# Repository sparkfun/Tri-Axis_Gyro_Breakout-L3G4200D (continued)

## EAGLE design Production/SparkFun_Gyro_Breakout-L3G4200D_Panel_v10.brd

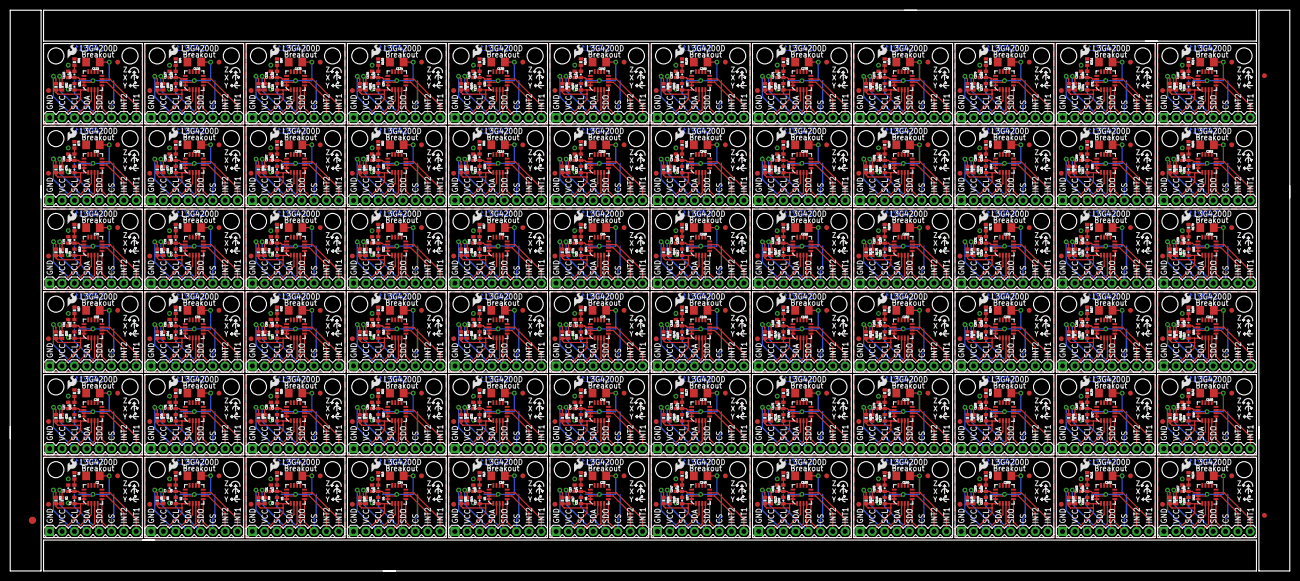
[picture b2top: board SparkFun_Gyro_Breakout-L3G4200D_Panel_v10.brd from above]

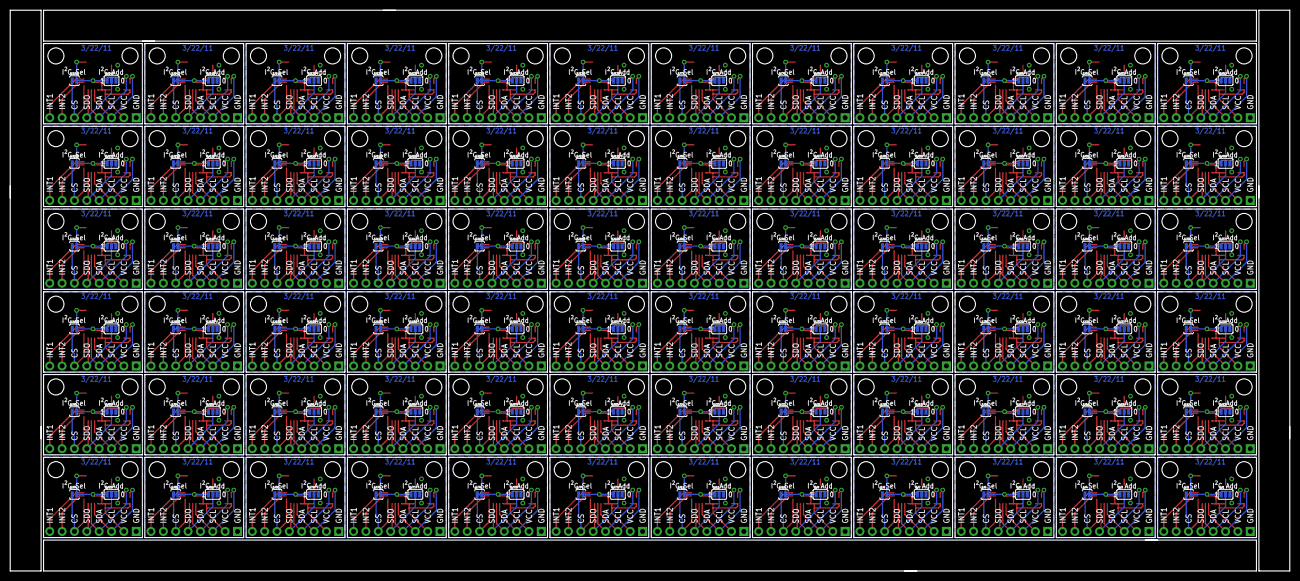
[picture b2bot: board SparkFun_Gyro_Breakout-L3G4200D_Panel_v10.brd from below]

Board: 2 copper layers, 263.1 x 115.3 mm, 1155 parts (144 on the bottom side), 720 nets.

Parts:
C1, C5, C9, C13, C17, C21, C25, C29, C33, C37, C41, C45, C49, C53, C57, C61, C65, C69, C73, C77, C81, C85, C89, C93, C97, C101, C105, C109, C113, C117, C121, C125, C129, C133, C137, C141, C145, C149, C153, C157, C161, C165, C169, C173, C177, C181, C185, C189, C193, C197, C201, C205, C209, C213, C217, C221, C225, C229, C233, C237, C241, C245, C249, C253, C257, C261, C265, C269, C273, C277, C281, C285: 0.1uF; 0402-CAP
C2, C6, C10, C14, C18, C22, C26, C30, C34, C38, C42, C46, C50, C54, C58, C62, C66, C70, C74, C78, C82, C86, C90, C94, C98, C102, C106, C110, C114, C118, C122, C126, C130, C134, C138, C142, C146, C150, C154, C158, C162, C166, C170, C174, C178, C182, C186, C190, C194, C198, C202, C206, C210, C214, C218, C222, C226, C230, C234, C238, C242, C246, C250, C254, C258, C262, C266, C270, C274, C278, C282, C286: 10uF; 1206
C3, C7, C11, C15, C19, C23, C27, C31, C35, C39, C43, C47, C51, C55, C59, C63, C67, C71, C75, C79, C83, C87, C91, C95, C99, C103, C107, C111, C115, C119, C123, C127, C131, C135, C139, C143, C147, C151, C155, C159, C163, C167, C171, C175, C179, C183, C187, C191, C195, C199, C203, C207, C211, C215, C219, C223, C227, C231, C235, C239, C243, C247, C251, C255, C259, C263, C267, C271, C275, C279, C283, C287: 10nF; 0402-CAP
C4, C8, C12, C16, C20, C24, C28, C32, C36, C40, C44, C48, C52, C56, C60, C64, C68, C72, C76, C80, C84, C88, C92, C96, C100, C104, C108, C112, C116, C120, C124, C128, C132, C136, C140, C144, C148, C152, C156, C160, C164, C168, C172, C176, C180, C184, C188, C192, C196, C200, C204, C208, C212, C216, C220, C224, C228, C232, C236, C240, C244, C248, C252, C256, C260, C264, C268, C272, C276, C280, C284, C288: 470nF; 0402-CAP
E$1: FIDUCIAL-1.5X3
E$5, E$6: FIDUCIAL-1X2
JP1, JP7, JP13, JP19, JP25, JP31, JP37, JP43, JP49, JP55, JP61, JP67, JP73, JP79, JP85, JP91, JP97, JP103, JP109, JP115, JP121, JP127, JP133, JP139, JP145, JP151, JP157, JP163, JP169, JP175, JP181, JP187, JP193, JP199, JP205, JP211, JP217, JP223, JP229, JP235, JP241, JP247, JP253, JP259, JP265, JP271, JP277, JP283, JP289, JP295, JP301, JP307, JP313, JP319, JP325, JP331, JP337, JP343, JP349, JP355, JP361, JP367, JP373, JP379, JP385, JP391, JP397, JP403, JP409, JP415, JP421, JP427: OUTPUT; 1X08
JP2, JP3, JP8, JP9, JP14, JP15, JP20, JP21, JP26, JP27, JP32, JP33, JP38, JP39, JP44, JP45, JP50, JP51, JP56, JP57, JP62, JP63, JP68, JP69, JP74, JP75, JP80, JP81, JP86, JP87, JP92, JP93, JP98, JP99, JP104, JP105, JP110, JP111, JP116, JP117, JP122, JP123, JP128, JP129, JP134, JP135, JP140, JP141, JP146, JP147, JP152, JP153, JP158, JP159, JP164, JP165, JP170, JP171, JP176, JP177, JP182, JP183, JP188, JP189, JP194, JP195, JP200, JP201, JP206, JP207, JP212, JP213, JP218, JP219, JP224, JP225, JP230, JP231, JP236, JP237, JP242, JP243, JP248, JP249, JP254, JP255, JP260, JP261, JP266, JP267, JP272, JP273, JP278, JP279, JP284, JP285, JP290, JP291, JP296, JP297, JP302, JP303, JP308, JP309, JP314, JP315, JP320, JP321, JP326, JP327, JP332, JP333, JP338, JP339, JP344, JP345, JP350, JP351, JP356, JP357, JP362, JP363, JP368, JP369, JP374, JP375, JP380, JP381, JP386, JP387, JP392, JP393, JP398, JP399, JP404, JP405, JP410, JP411, JP416, JP417, JP422, JP423, JP428, JP429: STAND-OFF
JP4, JP10, JP16, JP22, JP28, JP34, JP40, JP46, JP52, JP58, JP64, JP70, JP76, JP82, JP88, JP94, JP100, JP106, JP112, JP118, JP124, JP130, JP136, JP142, JP148, JP154, JP160, JP166, JP172, JP178, JP184, JP190, JP196, JP202, JP208, JP214, JP220, JP226, JP232, JP238, JP244, JP250, JP256, JP262, JP268, JP274, JP280, JP286, JP292, JP298, JP304, JP310, JP316, JP322, JP328, JP334, JP340, JP346, JP352, JP358, JP364, JP370, JP376, JP382, JP388, JP394, JP400, JP406, JP412, JP418, JP424, JP430: LOGO-SFESK; SFE-LOGO-FLAME
JP5, JP6, JP11, JP12, JP17, JP18, JP23, JP24, JP29, JP30, JP35, JP36, JP41, JP42, JP47, JP48, JP53, JP54, JP59, JP60, JP65, JP66, JP71, JP72, JP77, JP78, JP83, JP84, JP89, JP90, JP95, JP96, JP101, JP102, JP107, JP108, JP113, JP114, JP119, JP120, JP125, JP126, JP131, JP132, JP137, JP138, JP143, JP144, JP149, JP150, JP155, JP156, JP161, JP162, JP167, JP168, JP173, JP174, JP179, JP180, JP185, JP186, JP191, JP192, JP197, JP198, JP203, JP204, JP209, JP210, JP215, JP216, JP221, JP222, JP227, JP228, JP233, JP234, JP239, JP240, JP245, JP246, JP251, JP252, JP257, JP258, JP263, JP264, JP269, JP270, JP275, JP276, JP281, JP282, JP287, JP288, JP293, JP294, JP299, JP300, JP305, JP306, JP311, JP312, JP317, JP318, JP323, JP324, JP329, JP330, JP335, JP336, JP341, JP342, JP347, JP348, JP353, JP354, JP359, JP360, JP365, JP366, JP371, JP372, JP377, JP378, JP383, JP384, JP389, JP390, JP395, JP396, JP401, JP402, JP407, JP408, JP413, JP414, JP419, JP420, JP425, JP426, JP431, JP432: FIDUCIAL1X2; FIDUCIAL-1X2
R1, R2, R3, R4, R5, R6, R7, R8, R9, R10, R11, R12, R13, R14, R15, R16, R17, R18, R19, R20, R21, R22, R23, R24, R25, R26, R27, R28, R29, R30, R31, R32, R33, R34, R35, R36, R37, R38, R39, R40, R41, R42, R43, R44, R45, R46, R47, R48, R49, R50, R51, R52, R53, R54, R55, R56, R57, R58, R59, R60, R61, R62, R63, R64, R65, R66, R67, R68, R69, R70, R71, R72, R73, R74, R75, R76, R77, R78, R79, R80, R81, R82, R83, R84, R85, R86, R87, R88, R89, R90, R91, R92, R93, R94, R95, R96, R97, R98, R99, R100, R101, R102, R103, R104, R105, R106, R107, R108, R109, R110, R111, R112, R113, R114, R115, R116, R117, R118, R119, R120, R121, R122, R123, R124, R125, R126, R127, R128, R129, R130, R131, R132, R133, R134, R135, R136, R137, R138, R139, R140, R141, R142, R143, R144, R145, R146, R147, R148, R149, R150, R151, R152, R153, R154, R155, R156, R157, R158, R159, R160, R161, R162, R163, R164, R165, R166, R167, R168, R169, R170, R171, R172, R173, R174, R175, R176, R177, R178, R179, R180, R181, R182, R183, R184, R185, R186, R187, R188, R189, R190, R191, R192, R193, R194, R195, R196, R197, R198, R199, R200, R201, R202, R203, R204, R205, R206, R207, R208, R209, R210, R211, R212, R213, R214, R215, R216: 10k; 0402-RES
SJ1, SJ3, SJ5, SJ7, SJ9, SJ11, SJ13, SJ15, SJ17, SJ19, SJ21, SJ23, SJ25, SJ27, SJ29, SJ31, SJ33, SJ35, SJ37, SJ39, SJ41, SJ43, SJ45, SJ47, SJ49, SJ51, SJ53, SJ55, SJ57, SJ59, SJ61, SJ63, SJ65, SJ67, SJ69, SJ71, SJ73, SJ75, SJ77, SJ79, SJ81, SJ83, SJ85, SJ87, SJ89, SJ91, SJ93, SJ95, SJ97, SJ99, SJ101, SJ103, SJ105, SJ107, SJ109, SJ111, SJ113, SJ115, SJ117, SJ119, SJ121, SJ123, SJ125, SJ127, SJ129, SJ131, SJ133, SJ135, SJ137, SJ139, SJ141, SJ143: I2C-Add; SJ_3
SJ2, SJ4, SJ6, SJ8, SJ10, SJ12, SJ14, SJ16, SJ18, SJ20, SJ22, SJ24, SJ26, SJ28, SJ30, SJ32, SJ34, SJ36, SJ38, SJ40, SJ42, SJ44, SJ46, SJ48, SJ50, SJ52, SJ54, SJ56, SJ58, SJ60, SJ62, SJ64, SJ66, SJ68, SJ70, SJ72, SJ74, SJ76, SJ78, SJ80, SJ82, SJ84, SJ86, SJ88, SJ90, SJ92, SJ94, SJ96, SJ98, SJ100, SJ102, SJ104, SJ106, SJ108, SJ110, SJ112, SJ114, SJ116, SJ118, SJ120, SJ122, SJ124, SJ126, SJ128, SJ130, SJ132, SJ134, SJ136, SJ138, SJ140, SJ142, SJ144: I2C-Mode; SJ_2S-NO
U1, U2, U3, U4, U5, U6, U7, U8, U9, U10, U11, U12, U13, U14, U15, U16, U17, U18, U19, U20, U21, U22, U23, U24, U25, U26, U27, U28, U29, U30, U31, U32, U33, U34, U35, U36, U37, U38, U39, U40, U41, U42, U43, U44, U45, U46, U47, U48, U49, U50, U51, U52, U53, U54, U55, U56, U57, U58, U59, U60, U61, U62, U63, U64, U65, U66, U67, U68, U69, U70, U71, U72: L3G4200D; LGA16-4X4

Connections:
CS: JP1.6, SJ2.1, U1.5
CS1: JP7.6, SJ4.1, U2.5
CS2: JP13.6, SJ6.1, U3.5
CS3: JP19.6, SJ8.1, U4.5
CS4: JP25.6, SJ10.1, U5.5
CS5: JP31.6, SJ12.1, U6.5
CS6: JP37.6, SJ14.1, U7.5
CS7: JP43.6, SJ16.1, U8.5
CS8: JP49.6, SJ18.1, U9.5
CS9: JP55.6, SJ20.1, U10.5
CS10: JP61.6, SJ22.1, U11.5
CS11: JP67.6, SJ24.1, U12.5
CS12: JP73.6, SJ26.1, U13.5
CS13: JP79.6, SJ28.1, U14.5
CS14: JP85.6, SJ30.1, U15.5
CS15: JP91.6, SJ32.1, U16.5
CS16: JP97.6, SJ34.1, U17.5
CS17: JP103.6, SJ36.1, U18.5
CS18: JP109.6, SJ38.1, U19.5
CS19: JP115.6, SJ40.1, U20.5
CS20: JP121.6, SJ42.1, U21.5
CS21: JP127.6, SJ44.1, U22.5
CS22: JP133.6, SJ46.1, U23.5
CS23: JP139.6, SJ48.1, U24.5
CS24: JP145.6, SJ50.1, U25.5
CS25: JP151.6, SJ52.1, U26.5
CS26: JP157.6, SJ54.1, U27.5
CS27: JP163.6, SJ56.1, U28.5
CS28: JP169.6, SJ58.1, U29.5
CS29: JP175.6, SJ60.1, U30.5
CS30: JP181.6, SJ62.1, U31.5
CS31: JP187.6, SJ64.1, U32.5
CS32: JP193.6, SJ66.1, U33.5
CS33: JP199.6, SJ68.1, U34.5
CS34: JP205.6, SJ70.1, U35.5
CS35: JP211.6, SJ72.1, U36.5
CS36: JP217.6, SJ74.1, U37.5
CS37: JP223.6, SJ76.1, U38.5
CS38: JP229.6, SJ78.1, U39.5
CS39: JP235.6, SJ80.1, U40.5
CS40: JP241.6, SJ82.1, U41.5
CS41: JP247.6, SJ84.1, U42.5
CS42: JP253.6, SJ86.1, U43.5
CS43: JP259.6, SJ88.1, U44.5
CS44: JP265.6, SJ90.1, U45.5
CS45: JP271.6, SJ92.1, U46.5
CS46: JP277.6, SJ94.1, U47.5
CS47: JP283.6, SJ96.1, U48.5
CS48: JP289.6, SJ98.1, U49.5
CS49: JP295.6, SJ100.1, U50.5
CS50: JP301.6, SJ102.1, U51.5
CS51: JP307.6, SJ104.1, U52.5
CS52: JP313.6, SJ106.1, U53.5
CS53: JP319.6, SJ108.1, U54.5
CS54: JP325.6, SJ110.1, U55.5
CS55: JP331.6, SJ112.1, U56.5
CS56: JP337.6, SJ114.1, U57.5
CS57: JP343.6, SJ116.1, U58.5
CS58: JP349.6, SJ118.1, U59.5
CS59: JP355.6, SJ120.1, U60.5
CS60: JP361.6, SJ122.1, U61.5
CS61: JP367.6, SJ124.1, U62.5
CS62: JP373.6, SJ126.1, U63.5
CS63: JP379.6, SJ128.1, U64.5
CS64: JP385.6, SJ130.1, U65.5
CS65: JP391.6, SJ132.1, U66.5
CS66: JP397.6, SJ134.1, U67.5
CS67: JP403.6, SJ136.1, U68.5
CS68: JP409.6, SJ138.1, U69.5
CS69: JP415.6, SJ140.1, U70.5
CS70: JP421.6, SJ142.1, U71.5
CS71: JP427.6, SJ144.1, U72.5
GND: C1.2, C2.2, C3.2, JP1.1, R1.1, SJ1.3, U1.8, U1.9, U1.10, U1.11, U1.12, U1.13
GND1: C5.2, C6.2, C7.2, JP7.1, R4.1, SJ3.3, U2.8, U2.9, U2.10, U2.11, U2.12, U2.13
GND2: C9.2, C10.2, C11.2, JP13.1, R7.1, SJ5.3, U3.8, U3.9, U3.10, U3.11, U3.12, U3.13
GND3: C13.2, C14.2, C15.2, JP19.1, R10.1, SJ7.3, U4.8, U4.9, U4.10, U4.11, U4.12, U4.13
GND4: C17.2, C18.2, C19.2, JP25.1, R13.1, SJ9.3, U5.8, U5.9, U5.10, U5.11, U5.12, U5.13
GND5: C21.2, C22.2, C23.2, JP31.1, R16.1, SJ11.3, U6.8, U6.9, U6.10, U6.11, U6.12, U6.13
GND6: C25.2, C26.2, C27.2, JP37.1, R19.1, SJ13.3, U7.8, U7.9, U7.10, U7.11, U7.12, U7.13
GND7: C29.2, C30.2, C31.2, JP43.1, R22.1, SJ15.3, U8.8, U8.9, U8.10, U8.11, U8.12, U8.13
GND8: C33.2, C34.2, C35.2, JP49.1, R25.1, SJ17.3, U9.8, U9.9, U9.10, U9.11, U9.12, U9.13
GND9: C37.2, C38.2, C39.2, JP55.1, R28.1, SJ19.3, U10.8, U10.9, U10.10, U10.11, U10.12, U10.13
GND10: C41.2, C42.2, C43.2, JP61.1, R31.1, SJ21.3, U11.8, U11.9, U11.10, U11.11, U11.12, U11.13
GND11: C45.2, C46.2, C47.2, JP67.1, R34.1, SJ23.3, U12.8, U12.9, U12.10, U12.11, U12.12, U12.13
GND12: C49.2, C50.2, C51.2, JP73.1, R37.1, SJ25.3, U13.8, U13.9, U13.10, U13.11, U13.12, U13.13
GND13: C53.2, C54.2, C55.2, JP79.1, R40.1, SJ27.3, U14.8, U14.9, U14.10, U14.11, U14.12, U14.13
GND14: C57.2, C58.2, C59.2, JP85.1, R43.1, SJ29.3, U15.8, U15.9, U15.10, U15.11, U15.12, U15.13
GND15: C61.2, C62.2, C63.2, JP91.1, R46.1, SJ31.3, U16.8, U16.9, U16.10, U16.11, U16.12, U16.13
GND16: C65.2, C66.2, C67.2, JP97.1, R49.1, SJ33.3, U17.8, U17.9, U17.10, U17.11, U17.12, U17.13
GND17: C69.2, C70.2, C71.2, JP103.1, R52.1, SJ35.3, U18.8, U18.9, U18.10, U18.11, U18.12, U18.13
GND18: C73.2, C74.2, C75.2, JP109.1, R55.1, SJ37.3, U19.8, U19.9, U19.10, U19.11, U19.12, U19.13
GND19: C77.2, C78.2, C79.2, JP115.1, R58.1, SJ39.3, U20.8, U20.9, U20.10, U20.11, U20.12, U20.13
GND20: C81.2, C82.2, C83.2, JP121.1, R61.1, SJ41.3, U21.8, U21.9, U21.10, U21.11, U21.12, U21.13
GND21: C85.2, C86.2, C87.2, JP127.1, R64.1, SJ43.3, U22.8, U22.9, U22.10, U22.11, U22.12, U22.13
GND22: C89.2, C90.2, C91.2, JP133.1, R67.1, SJ45.3, U23.8, U23.9, U23.10, U23.11, U23.12, U23.13
GND23: C93.2, C94.2, C95.2, JP139.1, R70.1, SJ47.3, U24.8, U24.9, U24.10, U24.11, U24.12, U24.13
GND24: C97.2, C98.2, C99.2, JP145.1, R73.1, SJ49.3, U25.8, U25.9, U25.10, U25.11, U25.12, U25.13
GND25: C101.2, C102.2, C103.2, JP151.1, R76.1, SJ51.3, U26.8, U26.9, U26.10, U26.11, U26.12, U26.13
GND26: C105.2, C106.2, C107.2, JP157.1, R79.1, SJ53.3, U27.8, U27.9, U27.10, U27.11, U27.12, U27.13
GND27: C109.2, C110.2, C111.2, JP163.1, R82.1, SJ55.3, U28.8, U28.9, U28.10, U28.11, U28.12, U28.13
GND28: C113.2, C114.2, C115.2, JP169.1, R85.1, SJ57.3, U29.8, U29.9, U29.10, U29.11, U29.12, U29.13
GND29: C117.2, C118.2, C119.2, JP175.1, R88.1, SJ59.3, U30.8, U30.9, U30.10, U30.11, U30.12, U30.13
GND30: C121.2, C122.2, C123.2, JP181.1, R91.1, SJ61.3, U31.8, U31.9, U31.10, U31.11, U31.12, U31.13
GND31: C125.2, C126.2, C127.2, JP187.1, R94.1, SJ63.3, U32.8, U32.9, U32.10, U32.11, U32.12, U32.13
GND32: C129.2, C130.2, C131.2, JP193.1, R97.1, SJ65.3, U33.8, U33.9, U33.10, U33.11, U33.12, U33.13
GND33: C133.2, C134.2, C135.2, JP199.1, R100.1, SJ67.3, U34.8, U34.9, U34.10, U34.11, U34.12, U34.13
GND34: C137.2, C138.2, C139.2, JP205.1, R103.1, SJ69.3, U35.8, U35.9, U35.10, U35.11, U35.12, U35.13
GND35: C141.2, C142.2, C143.2, JP211.1, R106.1, SJ71.3, U36.8, U36.9, U36.10, U36.11, U36.12, U36.13
GND36: C145.2, C146.2, C147.2, JP217.1, R109.1, SJ73.3, U37.8, U37.9, U37.10, U37.11, U37.12, U37.13
GND37: C149.2, C150.2, C151.2, JP223.1, R112.1, SJ75.3, U38.8, U38.9, U38.10, U38.11, U38.12, U38.13
GND38: C153.2, C154.2, C155.2, JP229.1, R115.1, SJ77.3, U39.8, U39.9, U39.10, U39.11, U39.12, U39.13
GND39: C157.2, C158.2, C159.2, JP235.1, R118.1, SJ79.3, U40.8, U40.9, U40.10, U40.11, U40.12, U40.13
GND40: C161.2, C162.2, C163.2, JP241.1, R121.1, SJ81.3, U41.8, U41.9, U41.10, U41.11, U41.12, U41.13
GND41: C165.2, C166.2, C167.2, JP247.1, R124.1, SJ83.3, U42.8, U42.9, U42.10, U42.11, U42.12, U42.13
GND42: C169.2, C170.2, C171.2, JP253.1, R127.1, SJ85.3, U43.8, U43.9, U43.10, U43.11, U43.12, U43.13
GND43: C173.2, C174.2, C175.2, JP259.1, R130.1, SJ87.3, U44.8, U44.9, U44.10, U44.11, U44.12, U44.13
GND44: C177.2, C178.2, C179.2, JP265.1, R133.1, SJ89.3, U45.8, U45.9, U45.10, U45.11, U45.12, U45.13
GND45: C181.2, C182.2, C183.2, JP271.1, R136.1, SJ91.3, U46.8, U46.9, U46.10, U46.11, U46.12, U46.13
GND46: C185.2, C186.2, C187.2, JP277.1, R139.1, SJ93.3, U47.8, U47.9, U47.10, U47.11, U47.12, U47.13
GND47: C189.2, C190.2, C191.2, JP283.1, R142.1, SJ95.3, U48.8, U48.9, U48.10, U48.11, U48.12, U48.13
GND48: C193.2, C194.2, C195.2, JP289.1, R145.1, SJ97.3, U49.8, U49.9, U49.10, U49.11, U49.12, U49.13
GND49: C197.2, C198.2, C199.2, JP295.1, R148.1, SJ99.3, U50.8, U50.9, U50.10, U50.11, U50.12, U50.13
GND50: C201.2, C202.2, C203.2, JP301.1, R151.1, SJ101.3, U51.8, U51.9, U51.10, U51.11, U51.12, U51.13
GND51: C205.2, C206.2, C207.2, JP307.1, R154.1, SJ103.3, U52.8, U52.9, U52.10, U52.11, U52.12, U52.13
GND52: C209.2, C210.2, C211.2, JP313.1, R157.1, SJ105.3, U53.8, U53.9, U53.10, U53.11, U53.12, U53.13
GND53: C213.2, C214.2, C215.2, JP319.1, R160.1, SJ107.3, U54.8, U54.9, U54.10, U54.11, U54.12, U54.13
GND54: C217.2, C218.2, C219.2, JP325.1, R163.1, SJ109.3, U55.8, U55.9, U55.10, U55.11, U55.12, U55.13
GND55: C221.2, C222.2, C223.2, JP331.1, R166.1, SJ111.3, U56.8, U56.9, U56.10, U56.11, U56.12, U56.13
GND56: C225.2, C226.2, C227.2, JP337.1, R169.1, SJ113.3, U57.8, U57.9, U57.10, U57.11, U57.12, U57.13
GND57: C229.2, C230.2, C231.2, JP343.1, R172.1, SJ115.3, U58.8, U58.9, U58.10, U58.11, U58.12, U58.13
GND58: C233.2, C234.2, C235.2, JP349.1, R175.1, SJ117.3, U59.8, U59.9, U59.10, U59.11, U59.12, U59.13
GND59: C237.2, C238.2, C239.2, JP355.1, R178.1, SJ119.3, U60.8, U60.9, U60.10, U60.11, U60.12, U60.13
GND60: C241.2, C242.2, C243.2, JP361.1, R181.1, SJ121.3, U61.8, U61.9, U61.10, U61.11, U61.12, U61.13
GND61: C245.2, C246.2, C247.2, JP367.1, R184.1, SJ123.3, U62.8, U62.9, U62.10, U62.11, U62.12, U62.13
GND62: C249.2, C250.2, C251.2, JP373.1, R187.1, SJ125.3, U63.8, U63.9, U63.10, U63.11, U63.12, U63.13
GND63: C253.2, C254.2, C255.2, JP379.1, R190.1, SJ127.3, U64.8, U64.9, U64.10, U64.11, U64.12, U64.13
GND64: C257.2, C258.2, C259.2, JP385.1, R193.1, SJ129.3, U65.8, U65.9, U65.10, U65.11, U65.12, U65.13
GND65: C261.2, C262.2, C263.2, JP391.1, R196.1, SJ131.3, U66.8, U66.9, U66.10, U66.11, U66.12, U66.13
GND66: C265.2, C266.2, C267.2, JP397.1, R199.1, SJ133.3, U67.8, U67.9, U67.10, U67.11, U67.12, U67.13
GND67: C269.2, C270.2, C271.2, JP403.1, R202.1, SJ135.3, U68.8, U68.9, U68.10, U68.11, U68.12, U68.13
GND68: C273.2, C274.2, C275.2, JP409.1, R205.1, SJ137.3, U69.8, U69.9, U69.10, U69.11, U69.12, U69.13
GND69: C277.2, C278.2, C279.2, JP415.1, R208.1, SJ139.3, U70.8, U70.9, U70.10, U70.11, U70.12, U70.13
GND70: C281.2, C282.2, C283.2, JP421.1, R211.1, SJ141.3, U71.8, U71.9, U71.10, U71.11, U71.12, U71.13
GND71: C285.2, C286.2, C287.2, JP427.1, R214.1, SJ143.3, U72.8, U72.9, U72.10, U72.11, U72.12, U72.13
INT1: JP1.8, U1.7
INT2: JP1.7, U1.6
INT3: JP7.8, U2.7
INT4: JP7.7, U2.6
INT5: JP13.8, U3.7
INT6: JP13.7, U3.6
INT7: JP19.8, U4.7
INT8: JP19.7, U4.6
INT9: JP25.8, U5.7
INT10: JP25.7, U5.6
INT11: JP31.8, U6.7
INT12: JP31.7, U6.6
INT13: JP37.8, U7.7
INT14: JP37.7, U7.6
INT15: JP43.8, U8.7
INT16: JP43.7, U8.6
INT17: JP49.8, U9.7
INT18: JP49.7, U9.6
INT19: JP55.8, U10.7
INT20: JP55.7, U10.6
INT21: JP61.8, U11.7
INT22: JP61.7, U11.6
INT23: JP67.8, U12.7
INT24: JP67.7, U12.6
INT25: JP73.8, U13.7
INT26: JP73.7, U13.6
INT27: JP79.8, U14.7
INT28: JP79.7, U14.6
INT29: JP85.8, U15.7
INT30: JP85.7, U15.6
INT31: JP91.8, U16.7
INT32: JP91.7, U16.6
INT33: JP97.8, U17.7
INT34: JP97.7, U17.6
INT35: JP103.8, U18.7
INT36: JP103.7, U18.6
INT37: JP109.8, U19.7
INT38: JP109.7, U19.6
INT39: JP115.8, U20.7
INT40: JP115.7, U20.6
INT41: JP121.8, U21.7
INT42: JP121.7, U21.6
INT43: JP127.8, U22.7
INT44: JP127.7, U22.6
INT45: JP133.8, U23.7
INT46: JP133.7, U23.6
INT47: JP139.8, U24.7
INT48: JP139.7, U24.6
INT49: JP145.8, U25.7
INT50: JP145.7, U25.6
INT51: JP151.8, U26.7
INT52: JP151.7, U26.6
INT53: JP157.8, U27.7
INT54: JP157.7, U27.6
INT55: JP163.8, U28.7
INT56: JP163.7, U28.6
INT57: JP169.8, U29.7
INT58: JP169.7, U29.6
INT59: JP175.8, U30.7
INT60: JP175.7, U30.6
INT61: JP181.8, U31.7
INT62: JP181.7, U31.6
INT63: JP187.8, U32.7
INT64: JP187.7, U32.6
INT65: JP193.8, U33.7
INT66: JP193.7, U33.6
INT67: JP199.8, U34.7
INT68: JP199.7, U34.6
INT69: JP205.8, U35.7
INT70: JP205.7, U35.6
INT71: JP211.8, U36.7
INT72: JP211.7, U36.6
INT73: JP217.8, U37.7
INT74: JP217.7, U37.6
INT75: JP223.8, U38.7
INT76: JP223.7, U38.6
INT77: JP229.8, U39.7
INT78: JP229.7, U39.6
INT79: JP235.8, U40.7
INT80: JP235.7, U40.6
INT81: JP241.8, U41.7
INT82: JP241.7, U41.6
INT83: JP247.8, U42.7
INT84: JP247.7, U42.6
INT85: JP253.8, U43.7
INT86: JP253.7, U43.6
INT87: JP259.8, U44.7
INT88: JP259.7, U44.6
INT89: JP265.8, U45.7
INT90: JP265.7, U45.6
INT91: JP271.8, U46.7
INT92: JP271.7, U46.6
INT93: JP277.8, U47.7
INT94: JP277.7, U47.6
INT95: JP283.8, U48.7
INT96: JP283.7, U48.6
INT97: JP289.8, U49.7
INT98: JP289.7, U49.6
INT99: JP295.8, U50.7
INT100: JP295.7, U50.6
INT101: JP301.8, U51.7
INT102: JP301.7, U51.6
INT103: JP307.8, U52.7
INT104: JP307.7, U52.6
INT105: JP313.8, U53.7
INT106: JP313.7, U53.6
INT107: JP319.8, U54.7
INT108: JP319.7, U54.6
INT109: JP325.8, U55.7
INT110: JP325.7, U55.6
INT111: JP331.8, U56.7
INT112: JP331.7, U56.6
INT113: JP337.8, U57.7
INT114: JP337.7, U57.6
INT115: JP343.8, U58.7
INT116: JP343.7, U58.6
INT117: JP349.8, U59.7
INT118: JP349.7, U59.6
INT119: JP355.8, U60.7
INT120: JP355.7, U60.6
INT121: JP361.8, U61.7
INT122: JP361.7, U61.6
INT123: JP367.8, U62.7
INT124: JP367.7, U62.6
INT125: JP373.8, U63.7
INT126: JP373.7, U63.6
INT127: JP379.8, U64.7
INT128: JP379.7, U64.6
INT129: JP385.8, U65.7
INT130: JP385.7, U65.6
INT131: JP391.8, U66.7
INT132: JP391.7, U66.6
INT133: JP397.8, U67.7
INT134: JP397.7, U67.6
INT135: JP403.8, U68.7
INT136: JP403.7, U68.6
INT137: JP409.8, U69.7
INT138: JP409.7, U69.6
INT139: JP415.8, U70.7
INT140: JP415.7, U70.6
INT141: JP421.8, U71.7
INT142: JP421.7, U71.6
INT143: JP427.8, U72.7
INT144: JP427.7, U72.6
PLL: C3.1, C4.1, U1.14
PLL1: C7.1, C8.1, U2.14
PLL2: C11.1, C12.1, U3.14
PLL3: C15.1, C16.1, U4.14
PLL4: C19.1, C20.1, U5.14
PLL5: C23.1, C24.1, U6.14
PLL6: C27.1, C28.1, U7.14
PLL7: C31.1, C32.1, U8.14
PLL8: C35.1, C36.1, U9.14
PLL9: C39.1, C40.1, U10.14
PLL10: C43.1, C44.1, U11.14
PLL11: C47.1, C48.1, U12.14
PLL12: C51.1, C52.1, U13.14
PLL13: C55.1, C56.1, U14.14
PLL14: C59.1, C60.1, U15.14
PLL15: C63.1, C64.1, U16.14
PLL16: C67.1, C68.1, U17.14
PLL17: C71.1, C72.1, U18.14
PLL18: C75.1, C76.1, U19.14
PLL19: C79.1, C80.1, U20.14
PLL20: C83.1, C84.1, U21.14
PLL21: C87.1, C88.1, U22.14
PLL22: C91.1, C92.1, U23.14
PLL23: C95.1, C96.1, U24.14
PLL24: C99.1, C100.1, U25.14
PLL25: C103.1, C104.1, U26.14
PLL26: C107.1, C108.1, U27.14
PLL27: C111.1, C112.1, U28.14
PLL28: C115.1, C116.1, U29.14
PLL29: C119.1, C120.1, U30.14
PLL30: C123.1, C124.1, U31.14
PLL31: C127.1, C128.1, U32.14
PLL32: C131.1, C132.1, U33.14
PLL33: C135.1, C136.1, U34.14
PLL34: C139.1, C140.1, U35.14
PLL35: C143.1, C144.1, U36.14
PLL36: C147.1, C148.1, U37.14
PLL37: C151.1, C152.1, U38.14
PLL38: C155.1, C156.1, U39.14
PLL39: C159.1, C160.1, U40.14
PLL40: C163.1, C164.1, U41.14
PLL41: C167.1, C168.1, U42.14
PLL42: C171.1, C172.1, U43.14
PLL43: C175.1, C176.1, U44.14
PLL44: C179.1, C180.1, U45.14
PLL45: C183.1, C184.1, U46.14
PLL46: C187.1, C188.1, U47.14
PLL47: C191.1, C192.1, U48.14
PLL48: C195.1, C196.1, U49.14
PLL49: C199.1, C200.1, U50.14
PLL50: C203.1, C204.1, U51.14
PLL51: C207.1, C208.1, U52.14
PLL52: C211.1, C212.1, U53.14
PLL53: C215.1, C216.1, U54.14
PLL54: C219.1, C220.1, U55.14
PLL55: C223.1, C224.1, U56.14
PLL56: C227.1, C228.1, U57.14
PLL57: C231.1, C232.1, U58.14
PLL58: C235.1, C236.1, U59.14
PLL59: C239.1, C240.1, U60.14
PLL60: C243.1, C244.1, U61.14
PLL61: C247.1, C248.1, U62.14
PLL62: C251.1, C252.1, U63.14
PLL63: C255.1, C256.1, U64.14
PLL64: C259.1, C260.1, U65.14
PLL65: C263.1, C264.1, U66.14
PLL66: C267.1, C268.1, U67.14
PLL67: C271.1, C272.1, U68.14
PLL68: C275.1, C276.1, U69.14
PLL69: C279.1, C280.1, U70.14
PLL70: C283.1, C284.1, U71.14
PLL71: C287.1, C288.1, U72.14
PLL-1: C8.2, R4.2
PLL-2: C4.2, R1.2
PLL-3: C12.2, R7.2
PLL-4: C16.2, R10.2
PLL-5: C20.2, R13.2
PLL-6: C24.2, R16.2
PLL-7: C28.2, R19.2
PLL-8: C32.2, R22.2
PLL-9: C36.2, R25.2
PLL-10: C40.2, R28.2
PLL-11: C44.2, R31.2
PLL-12: C48.2, R34.2
PLL-13: C52.2, R37.2
PLL-14: C56.2, R40.2
PLL-15: C60.2, R43.2
PLL-16: C64.2, R46.2
PLL-17: C68.2, R49.2
PLL-18: C72.2, R52.2
PLL-19: C76.2, R55.2
PLL-20: C80.2, R58.2
PLL-21: C84.2, R61.2
PLL-22: C88.2, R64.2
PLL-23: C92.2, R67.2
PLL-24: C96.2, R70.2
PLL-25: C100.2, R73.2
PLL-26: C104.2, R76.2
PLL-27: C108.2, R79.2
PLL-28: C112.2, R82.2
PLL-29: C116.2, R85.2
PLL-30: C120.2, R88.2
PLL-31: C124.2, R91.2
PLL-32: C128.2, R94.2
PLL-33: C132.2, R97.2
PLL-34: C136.2, R100.2
PLL-35: C140.2, R103.2
PLL-36: C144.2, R106.2
PLL-37: C148.2, R109.2
PLL-38: C152.2, R112.2
PLL-39: C156.2, R115.2
PLL-40: C160.2, R118.2
PLL-41: C164.2, R121.2
PLL-42: C168.2, R124.2
PLL-43: C172.2, R127.2
PLL-44: C176.2, R130.2
PLL-45: C180.2, R133.2
PLL-46: C184.2, R136.2
PLL-47: C188.2, R139.2
PLL-48: C192.2, R142.2
PLL-49: C196.2, R145.2
PLL-50: C200.2, R148.2
PLL-51: C204.2, R151.2
PLL-52: C208.2, R154.2
PLL-53: C212.2, R157.2
PLL-54: C216.2, R160.2
PLL-55: C220.2, R163.2
PLL-56: C224.2, R166.2
PLL-57: C228.2, R169.2
PLL-58: C232.2, R172.2
PLL-59: C236.2, R175.2
PLL-60: C240.2, R178.2
PLL-61: C244.2, R181.2
PLL-62: C248.2, R184.2
PLL-63: C252.2, R187.2
PLL-64: C256.2, R190.2
PLL-65: C260.2, R193.2
PLL-66: C264.2, R196.2
PLL-67: C268.2, R199.2
PLL-68: C272.2, R202.2
PLL-69: C276.2, R205.2
PLL-70: C280.2, R208.2
PLL-71: C284.2, R211.2
PLL-72: C288.2, R214.2
SCL: JP1.3, R3.1, U1.2
SCL1: JP7.3, R6.1, U2.2
SCL2: JP13.3, R9.1, U3.2
SCL3: JP19.3, R12.1, U4.2
SCL4: JP25.3, R15.1, U5.2
SCL5: JP31.3, R18.1, U6.2
SCL6: JP37.3, R21.1, U7.2
SCL7: JP43.3, R24.1, U8.2
SCL8: JP49.3, R27.1, U9.2
SCL9: JP55.3, R30.1, U10.2
SCL10: JP61.3, R33.1, U11.2
SCL11: JP67.3, R36.1, U12.2
SCL12: JP73.3, R39.1, U13.2
SCL13: JP79.3, R42.1, U14.2
SCL14: JP85.3, R45.1, U15.2
SCL15: JP91.3, R48.1, U16.2
SCL16: JP97.3, R51.1, U17.2
SCL17: JP103.3, R54.1, U18.2
SCL18: JP109.3, R57.1, U19.2
SCL19: JP115.3, R60.1, U20.2
SCL20: JP121.3, R63.1, U21.2
SCL21: JP127.3, R66.1, U22.2
SCL22: JP133.3, R69.1, U23.2
SCL23: JP139.3, R72.1, U24.2
SCL24: JP145.3, R75.1, U25.2
SCL25: JP151.3, R78.1, U26.2
SCL26: JP157.3, R81.1, U27.2
SCL27: JP163.3, R84.1, U28.2
SCL28: JP169.3, R87.1, U29.2
SCL29: JP175.3, R90.1, U30.2
SCL30: JP181.3, R93.1, U31.2
SCL31: JP187.3, R96.1, U32.2
SCL32: JP193.3, R99.1, U33.2
SCL33: JP199.3, R102.1, U34.2
SCL34: JP205.3, R105.1, U35.2
SCL35: JP211.3, R108.1, U36.2
SCL36: JP217.3, R111.1, U37.2
SCL37: JP223.3, R114.1, U38.2
SCL38: JP229.3, R117.1, U39.2
SCL39: JP235.3, R120.1, U40.2
SCL40: JP241.3, R123.1, U41.2
SCL41: JP247.3, R126.1, U42.2
SCL42: JP253.3, R129.1, U43.2
SCL43: JP259.3, R132.1, U44.2
SCL44: JP265.3, R135.1, U45.2
SCL45: JP271.3, R138.1, U46.2
SCL46: JP277.3, R141.1, U47.2
SCL47: JP283.3, R144.1, U48.2
SCL48: JP289.3, R147.1, U49.2
SCL49: JP295.3, R150.1, U50.2
SCL50: JP301.3, R153.1, U51.2
SCL51: JP307.3, R156.1, U52.2
SCL52: JP313.3, R159.1, U53.2
SCL53: JP319.3, R162.1, U54.2
SCL54: JP325.3, R165.1, U55.2
SCL55: JP331.3, R168.1, U56.2
SCL56: JP337.3, R171.1, U57.2
SCL57: JP343.3, R174.1, U58.2
SCL58: JP349.3, R177.1, U59.2
SCL59: JP355.3, R180.1, U60.2
SCL60: JP361.3, R183.1, U61.2
SCL61: JP367.3, R186.1, U62.2
SCL62: JP373.3, R189.1, U63.2
SCL63: JP379.3, R192.1, U64.2
SCL64: JP385.3, R195.1, U65.2
SCL65: JP391.3, R198.1, U66.2
SCL66: JP397.3, R201.1, U67.2
SCL67: JP403.3, R204.1, U68.2
SCL68: JP409.3, R207.1, U69.2
SCL69: JP415.3, R210.1, U70.2
SCL70: JP421.3, R213.1, U71.2
SCL71: JP427.3, R216.1, U72.2
SDA: JP1.4, R2.1, U1.3
SDA1: JP7.4, R5.1, U2.3
SDA2: JP13.4, R8.1, U3.3
SDA3: JP19.4, R11.1, U4.3
SDA4: JP25.4, R14.1, U5.3
SDA5: JP31.4, R17.1, U6.3
SDA6: JP37.4, R20.1, U7.3
SDA7: JP43.4, R23.1, U8.3
SDA8: JP49.4, R26.1, U9.3
SDA9: JP55.4, R29.1, U10.3
SDA10: JP61.4, R32.1, U11.3
SDA11: JP67.4, R35.1, U12.3
SDA12: JP73.4, R38.1, U13.3
SDA13: JP79.4, R41.1, U14.3
SDA14: JP85.4, R44.1, U15.3
SDA15: JP91.4, R47.1, U16.3
SDA16: JP97.4, R50.1, U17.3
SDA17: JP103.4, R53.1, U18.3
SDA18: JP109.4, R56.1, U19.3
SDA19: JP115.4, R59.1, U20.3
SDA20: JP121.4, R62.1, U21.3
SDA21: JP127.4, R65.1, U22.3
SDA22: JP133.4, R68.1, U23.3
SDA23: JP139.4, R71.1, U24.3
SDA24: JP145.4, R74.1, U25.3
SDA25: JP151.4, R77.1, U26.3
SDA26: JP157.4, R80.1, U27.3
SDA27: JP163.4, R83.1, U28.3
SDA28: JP169.4, R86.1, U29.3
SDA29: JP175.4, R89.1, U30.3
SDA30: JP181.4, R92.1, U31.3
SDA31: JP187.4, R95.1, U32.3
SDA32: JP193.4, R98.1, U33.3
SDA33: JP199.4, R101.1, U34.3
SDA34: JP205.4, R104.1, U35.3
SDA35: JP211.4, R107.1, U36.3
SDA36: JP217.4, R110.1, U37.3
SDA37: JP223.4, R113.1, U38.3
SDA38: JP229.4, R116.1, U39.3
SDA39: JP235.4, R119.1, U40.3
SDA40: JP241.4, R122.1, U41.3
SDA41: JP247.4, R125.1, U42.3
SDA42: JP253.4, R128.1, U43.3
SDA43: JP259.4, R131.1, U44.3
SDA44: JP265.4, R134.1, U45.3
SDA45: JP271.4, R137.1, U46.3
SDA46: JP277.4, R140.1, U47.3
SDA47: JP283.4, R143.1, U48.3
SDA48: JP289.4, R146.1, U49.3
SDA49: JP295.4, R149.1, U50.3
SDA50: JP301.4, R152.1, U51.3
SDA51: JP307.4, R155.1, U52.3
SDA52: JP313.4, R158.1, U53.3
SDA53: JP319.4, R161.1, U54.3
SDA54: JP325.4, R164.1, U55.3
SDA55: JP331.4, R167.1, U56.3
SDA56: JP337.4, R170.1, U57.3
SDA57: JP343.4, R173.1, U58.3
SDA58: JP349.4, R176.1, U59.3
SDA59: JP355.4, R179.1, U60.3
SDA60: JP361.4, R182.1, U61.3
SDA61: JP367.4, R185.1, U62.3
SDA62: JP373.4, R188.1, U63.3
SDA63: JP379.4, R191.1, U64.3
SDA64: JP385.4, R194.1, U65.3
SDA65: JP391.4, R197.1, U66.3
SDA66: JP397.4, R200.1, U67.3
SDA67: JP403.4, R203.1, U68.3
SDA68: JP409.4, R206.1, U69.3
SDA69: JP415.4, R209.1, U70.3
SDA70: JP421.4, R212.1, U71.3
SDA71: JP427.4, R215.1, U72.3
SDO: JP1.5, SJ1.2, U1.4
SDO1: JP7.5, SJ3.2, U2.4
SDO2: JP13.5, SJ5.2, U3.4
SDO3: JP19.5, SJ7.2, U4.4
SDO4: JP25.5, SJ9.2, U5.4
SDO5: JP31.5, SJ11.2, U6.4
SDO6: JP37.5, SJ13.2, U7.4
SDO7: JP43.5, SJ15.2, U8.4
SDO8: JP49.5, SJ17.2, U9.4
SDO9: JP55.5, SJ19.2, U10.4
SDO10: JP61.5, SJ21.2, U11.4
SDO11: JP67.5, SJ23.2, U12.4
SDO12: JP73.5, SJ25.2, U13.4
SDO13: JP79.5, SJ27.2, U14.4
SDO14: JP85.5, SJ29.2, U15.4
SDO15: JP91.5, SJ31.2, U16.4
SDO16: JP97.5, SJ33.2, U17.4
SDO17: JP103.5, SJ35.2, U18.4
SDO18: JP109.5, SJ37.2, U19.4
SDO19: JP115.5, SJ39.2, U20.4
SDO20: JP121.5, SJ41.2, U21.4
SDO21: JP127.5, SJ43.2, U22.4
SDO22: JP133.5, SJ45.2, U23.4
SDO23: JP139.5, SJ47.2, U24.4
SDO24: JP145.5, SJ49.2, U25.4
SDO25: JP151.5, SJ51.2, U26.4
SDO26: JP157.5, SJ53.2, U27.4
SDO27: JP163.5, SJ55.2, U28.4
SDO28: JP169.5, SJ57.2, U29.4
SDO29: JP175.5, SJ59.2, U30.4
SDO30: JP181.5, SJ61.2, U31.4
SDO31: JP187.5, SJ63.2, U32.4
SDO32: JP193.5, SJ65.2, U33.4
SDO33: JP199.5, SJ67.2, U34.4
SDO34: JP205.5, SJ69.2, U35.4
SDO35: JP211.5, SJ71.2, U36.4
SDO36: JP217.5, SJ73.2, U37.4
SDO37: JP223.5, SJ75.2, U38.4
SDO38: JP229.5, SJ77.2, U39.4
SDO39: JP235.5, SJ79.2, U40.4
SDO40: JP241.5, SJ81.2, U41.4
SDO41: JP247.5, SJ83.2, U42.4
SDO42: JP253.5, SJ85.2, U43.4
SDO43: JP259.5, SJ87.2, U44.4
SDO44: JP265.5, SJ89.2, U45.4
SDO45: JP271.5, SJ91.2, U46.4
SDO46: JP277.5, SJ93.2, U47.4
SDO47: JP283.5, SJ95.2, U48.4
SDO48: JP289.5, SJ97.2, U49.4
SDO49: JP295.5, SJ99.2, U50.4
SDO50: JP301.5, SJ101.2, U51.4
SDO51: JP307.5, SJ103.2, U52.4
SDO52: JP313.5, SJ105.2, U53.4
SDO53: JP319.5, SJ107.2, U54.4
SDO54: JP325.5, SJ109.2, U55.4
SDO55: JP331.5, SJ111.2, U56.4
SDO56: JP337.5, SJ113.2, U57.4
SDO57: JP343.5, SJ115.2, U58.4
SDO58: JP349.5, SJ117.2, U59.4
SDO59: JP355.5, SJ119.2, U60.4
SDO60: JP361.5, SJ121.2, U61.4
SDO61: JP367.5, SJ123.2, U62.4
SDO62: JP373.5, SJ125.2, U63.4
SDO63: JP379.5, SJ127.2, U64.4
SDO64: JP385.5, SJ129.2, U65.4
SDO65: JP391.5, SJ131.2, U66.4
SDO66: JP397.5, SJ133.2, U67.4
SDO67: JP403.5, SJ135.2, U68.4
SDO68: JP409.5, SJ137.2, U69.4
SDO69: JP415.5, SJ139.2, U70.4
SDO70: JP421.5, SJ141.2, U71.4
SDO71: JP427.5, SJ143.2, U72.4
VCC: C1.1, C2.1, JP1.2, R2.2, R3.2, SJ1.1, SJ2.2, U1.1, U1.15, U1.16
VCC1: C5.1, C6.1, JP7.2, R5.2, R6.2, SJ3.1, SJ4.2, U2.1, U2.15, U2.16
VCC2: C9.1, C10.1, JP13.2, R8.2, R9.2, SJ5.1, SJ6.2, U3.1, U3.15, U3.16
VCC3: C13.1, C14.1, JP19.2, R11.2, R12.2, SJ7.1, SJ8.2, U4.1, U4.15, U4.16
VCC4: C17.1, C18.1, JP25.2, R14.2, R15.2, SJ9.1, SJ10.2, U5.1, U5.15, U5.16
VCC5: C21.1, C22.1, JP31.2, R17.2, R18.2, SJ11.1, SJ12.2, U6.1, U6.15, U6.16
VCC6: C25.1, C26.1, JP37.2, R20.2, R21.2, SJ13.1, SJ14.2, U7.1, U7.15, U7.16
VCC7: C29.1, C30.1, JP43.2, R23.2, R24.2, SJ15.1, SJ16.2, U8.1, U8.15, U8.16
VCC8: C33.1, C34.1, JP49.2, R26.2, R27.2, SJ17.1, SJ18.2, U9.1, U9.15, U9.16
VCC9: C37.1, C38.1, JP55.2, R29.2, R30.2, SJ19.1, SJ20.2, U10.1, U10.15, U10.16
VCC10: C41.1, C42.1, JP61.2, R32.2, R33.2, SJ21.1, SJ22.2, U11.1, U11.15, U11.16
VCC11: C45.1, C46.1, JP67.2, R35.2, R36.2, SJ23.1, SJ24.2, U12.1, U12.15, U12.16
VCC12: C49.1, C50.1, JP73.2, R38.2, R39.2, SJ25.1, SJ26.2, U13.1, U13.15, U13.16
VCC13: C53.1, C54.1, JP79.2, R41.2, R42.2, SJ27.1, SJ28.2, U14.1, U14.15, U14.16
VCC14: C57.1, C58.1, JP85.2, R44.2, R45.2, SJ29.1, SJ30.2, U15.1, U15.15, U15.16
VCC15: C61.1, C62.1, JP91.2, R47.2, R48.2, SJ31.1, SJ32.2, U16.1, U16.15, U16.16
VCC16: C65.1, C66.1, JP97.2, R50.2, R51.2, SJ33.1, SJ34.2, U17.1, U17.15, U17.16
VCC17: C69.1, C70.1, JP103.2, R53.2, R54.2, SJ35.1, SJ36.2, U18.1, U18.15, U18.16
VCC18: C73.1, C74.1, JP109.2, R56.2, R57.2, SJ37.1, SJ38.2, U19.1, U19.15, U19.16
VCC19: C77.1, C78.1, JP115.2, R59.2, R60.2, SJ39.1, SJ40.2, U20.1, U20.15, U20.16
VCC20: C81.1, C82.1, JP121.2, R62.2, R63.2, SJ41.1, SJ42.2, U21.1, U21.15, U21.16
VCC21: C85.1, C86.1, JP127.2, R65.2, R66.2, SJ43.1, SJ44.2, U22.1, U22.15, U22.16
VCC22: C89.1, C90.1, JP133.2, R68.2, R69.2, SJ45.1, SJ46.2, U23.1, U23.15, U23.16
VCC23: C93.1, C94.1, JP139.2, R71.2, R72.2, SJ47.1, SJ48.2, U24.1, U24.15, U24.16
VCC24: C97.1, C98.1, JP145.2, R74.2, R75.2, SJ49.1, SJ50.2, U25.1, U25.15, U25.16
VCC25: C101.1, C102.1, JP151.2, R77.2, R78.2, SJ51.1, SJ52.2, U26.1, U26.15, U26.16
VCC26: C105.1, C106.1, JP157.2, R80.2, R81.2, SJ53.1, SJ54.2, U27.1, U27.15, U27.16
VCC27: C109.1, C110.1, JP163.2, R83.2, R84.2, SJ55.1, SJ56.2, U28.1, U28.15, U28.16
VCC28: C113.1, C114.1, JP169.2, R86.2, R87.2, SJ57.1, SJ58.2, U29.1, U29.15, U29.16
VCC29: C117.1, C118.1, JP175.2, R89.2, R90.2, SJ59.1, SJ60.2, U30.1, U30.15, U30.16
VCC30: C121.1, C122.1, JP181.2, R92.2, R93.2, SJ61.1, SJ62.2, U31.1, U31.15, U31.16
VCC31: C125.1, C126.1, JP187.2, R95.2, R96.2, SJ63.1, SJ64.2, U32.1, U32.15, U32.16
VCC32: C129.1, C130.1, JP193.2, R98.2, R99.2, SJ65.1, SJ66.2, U33.1, U33.15, U33.16
VCC33: C133.1, C134.1, JP199.2, R101.2, R102.2, SJ67.1, SJ68.2, U34.1, U34.15, U34.16
VCC34: C137.1, C138.1, JP205.2, R104.2, R105.2, SJ69.1, SJ70.2, U35.1, U35.15, U35.16
VCC35: C141.1, C142.1, JP211.2, R107.2, R108.2, SJ71.1, SJ72.2, U36.1, U36.15, U36.16
VCC36: C145.1, C146.1, JP217.2, R110.2, R111.2, SJ73.1, SJ74.2, U37.1, U37.15, U37.16
VCC37: C149.1, C150.1, JP223.2, R113.2, R114.2, SJ75.1, SJ76.2, U38.1, U38.15, U38.16
VCC38: C153.1, C154.1, JP229.2, R116.2, R117.2, SJ77.1, SJ78.2, U39.1, U39.15, U39.16
VCC39: C157.1, C158.1, JP235.2, R119.2, R120.2, SJ79.1, SJ80.2, U40.1, U40.15, U40.16
VCC40: C161.1, C162.1, JP241.2, R122.2, R123.2, SJ81.1, SJ82.2, U41.1, U41.15, U41.16
VCC41: C165.1, C166.1, JP247.2, R125.2, R126.2, SJ83.1, SJ84.2, U42.1, U42.15, U42.16
VCC42: C169.1, C170.1, JP253.2, R128.2, R129.2, SJ85.1, SJ86.2, U43.1, U43.15, U43.16
VCC43: C173.1, C174.1, JP259.2, R131.2, R132.2, SJ87.1, SJ88.2, U44.1, U44.15, U44.16
VCC44: C177.1, C178.1, JP265.2, R134.2, R135.2, SJ89.1, SJ90.2, U45.1, U45.15, U45.16
VCC45: C181.1, C182.1, JP271.2, R137.2, R138.2, SJ91.1, SJ92.2, U46.1, U46.15, U46.16
VCC46: C185.1, C186.1, JP277.2, R140.2, R141.2, SJ93.1, SJ94.2, U47.1, U47.15, U47.16
VCC47: C189.1, C190.1, JP283.2, R143.2, R144.2, SJ95.1, SJ96.2, U48.1, U48.15, U48.16
VCC48: C193.1, C194.1, JP289.2, R146.2, R147.2, SJ97.1, SJ98.2, U49.1, U49.15, U49.16
VCC49: C197.1, C198.1, JP295.2, R149.2, R150.2, SJ99.1, SJ100.2, U50.1, U50.15, U50.16
VCC50: C201.1, C202.1, JP301.2, R152.2, R153.2, SJ101.1, SJ102.2, U51.1, U51.15, U51.16
VCC51: C205.1, C206.1, JP307.2, R155.2, R156.2, SJ103.1, SJ104.2, U52.1, U52.15, U52.16
VCC52: C209.1, C210.1, JP313.2, R158.2, R159.2, SJ105.1, SJ106.2, U53.1, U53.15, U53.16
VCC53: C213.1, C214.1, JP319.2, R161.2, R162.2, SJ107.1, SJ108.2, U54.1, U54.15, U54.16
VCC54: C217.1, C218.1, JP325.2, R164.2, R165.2, SJ109.1, SJ110.2, U55.1, U55.15, U55.16
VCC55: C221.1, C222.1, JP331.2, R167.2, R168.2, SJ111.1, SJ112.2, U56.1, U56.15, U56.16
VCC56: C225.1, C226.1, JP337.2, R170.2, R171.2, SJ113.1, SJ114.2, U57.1, U57.15, U57.16
VCC57: C229.1, C230.1, JP343.2, R173.2, R174.2, SJ115.1, SJ116.2, U58.1, U58.15, U58.16
VCC58: C233.1, C234.1, JP349.2, R176.2, R177.2, SJ117.1, SJ118.2, U59.1, U59.15, U59.16
VCC59: C237.1, C238.1, JP355.2, R179.2, R180.2, SJ119.1, SJ120.2, U60.1, U60.15, U60.16
VCC60: C241.1, C242.1, JP361.2, R182.2, R183.2, SJ121.1, SJ122.2, U61.1, U61.15, U61.16
VCC61: C245.1, C246.1, JP367.2, R185.2, R186.2, SJ123.1, SJ124.2, U62.1, U62.15, U62.16
VCC62: C249.1, C250.1, JP373.2, R188.2, R189.2, SJ125.1, SJ126.2, U63.1, U63.15, U63.16
VCC63: C253.1, C254.1, JP379.2, R191.2, R192.2, SJ127.1, SJ128.2, U64.1, U64.15, U64.16
VCC64: C257.1, C258.1, JP385.2, R194.2, R195.2, SJ129.1, SJ130.2, U65.1, U65.15, U65.16
VCC65: C261.1, C262.1, JP391.2, R197.2, R198.2, SJ131.1, SJ132.2, U66.1, U66.15, U66.16
VCC66: C265.1, C266.1, JP397.2, R200.2, R201.2, SJ133.1, SJ134.2, U67.1, U67.15, U67.16
VCC67: C269.1, C270.1, JP403.2, R203.2, R204.2, SJ135.1, SJ136.2, U68.1, U68.15, U68.16
VCC68: C273.1, C274.1, JP409.2, R206.2, R207.2, SJ137.1, SJ138.2, U69.1, U69.15, U69.16
VCC69: C277.1, C278.1, JP415.2, R209.2, R210.2, SJ139.1, SJ140.2, U70.1, U70.15, U70.16
VCC70: C281.1, C282.1, JP421.2, R212.2, R213.2, SJ141.1, SJ142.2, U71.1, U71.15, U71.16
VCC71: C285.1, C286.1, JP427.2, R215.2, R216.2, SJ143.1, SJ144.2, U72.1, U72.15, U72.16

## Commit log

2015-05-07 Adding hardware, example code files
2015-10-19 created panel v10
